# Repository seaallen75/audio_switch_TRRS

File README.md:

# audio_switch_TRRS
A 3.5mm TRRS audio switch, COM to A or B

I got tired of fumbling around under my desk to switch my audio connection between a headset and a speaker bar so I created a simple 3.5mm TRRS audio switch with KiCad and FreeCAD. 

The PCB was designed in KiCad. The gerbers can be found in gerbers/audio_switch_gerbers.zip and can be sent to any PCB fabricator. The PCB should be made 1.6mm thick to fit with the case. The [toggle switch](https://www.digikey.com/en/products/detail/e-switch/1003P1T1B1M2QEH/378894) and [3.5mm audio jacks](https://www.digikey.com/en/products/detail/tensility-international-corp/54-00174/12140150) are soldered to the PCB. 

The case was designed in FreeCAD. The .step models are available as well as a Bambu Studio file (.3mf) for printing on a Bambu 3D printer. M2.5x4x3.5 threaded heat-set inserts are pressed into the front piece of the case. A vertical heat-set insert press tool makes it much easier to install all of the threaded inserts straight up and down. The back piece of the case is secured with M2.5x10 screws. The case is designed to be mounted with Kreg pocket-hole screws.

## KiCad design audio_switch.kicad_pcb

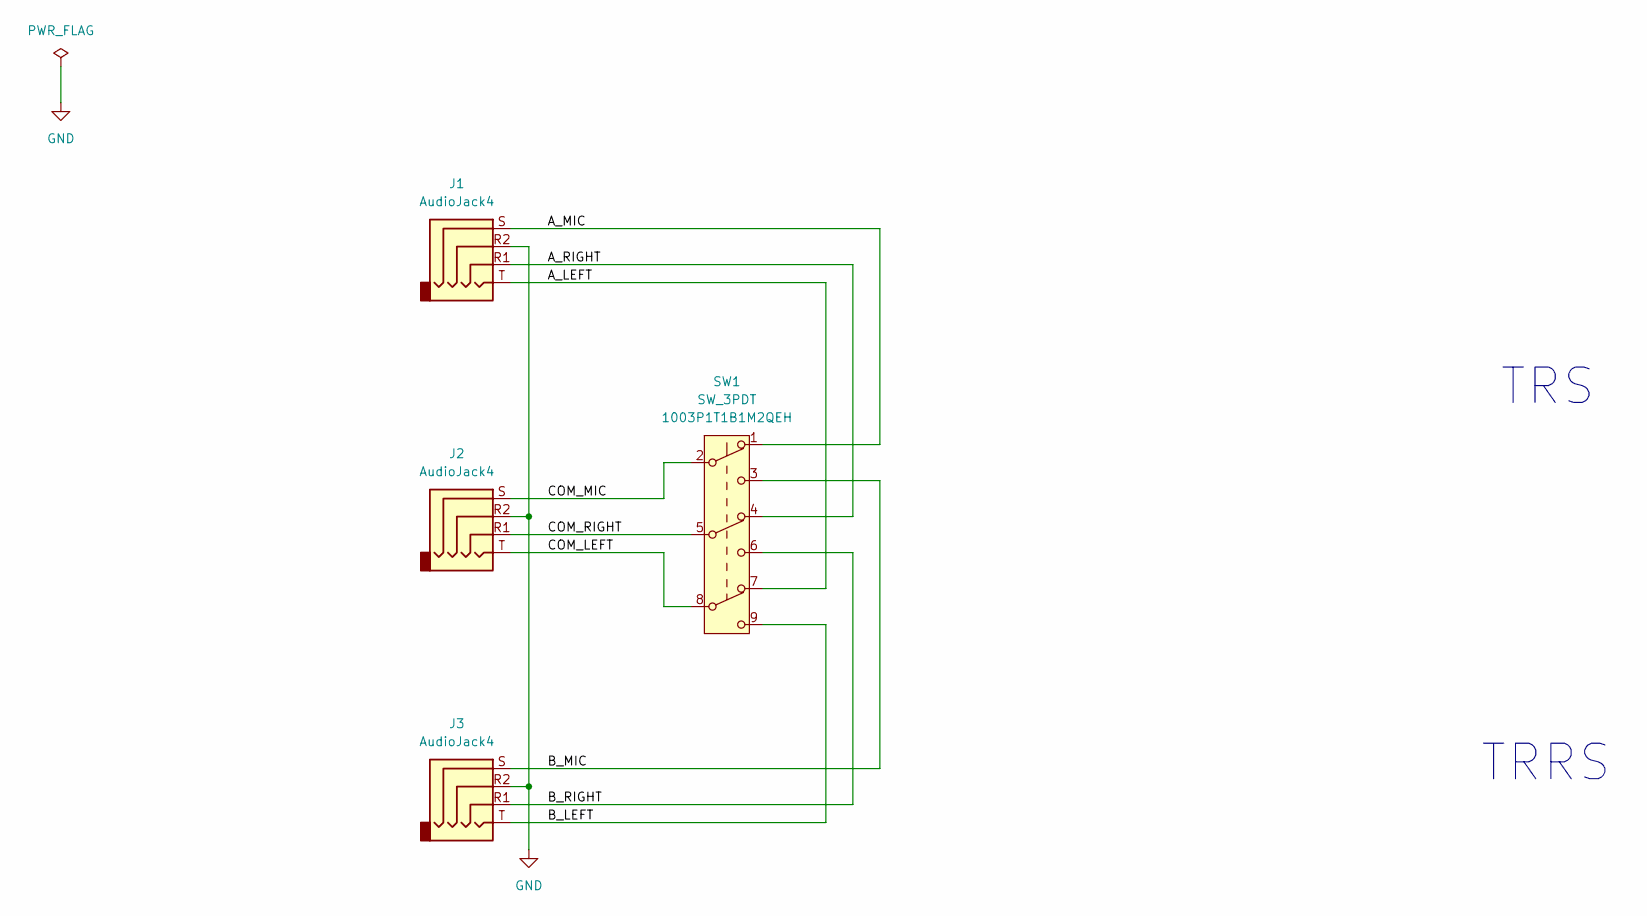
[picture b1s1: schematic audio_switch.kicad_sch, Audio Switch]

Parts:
J1, J2, J3: AudioJack4; 54-00174; MPN 54-00174
SW1: SW_3PDT; 1003P1T1B1M2QEH; MPN 1003P1T1B1M2QEH

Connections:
/A_LEFT: J1.T, SW1.7 (A)
/A_MIC: J1.S, SW1.1 (A)
/A_RIGHT: J1.R1, SW1.4 (A)
/B_LEFT: J3.T, SW1.9 (C)
/B_MIC: J3.S, SW1.3 (C)
/B_RIGHT: J3.R1, SW1.6 (C)
/COM_LEFT: J2.T, SW1.8 (B)
/COM_MIC: J2.S, SW1.2 (B)
/COM_RIGHT: J2.R1, SW1.5 (B)
GND: J1.R2, J2.R2, J3.R2

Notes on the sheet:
TRS
TRRS

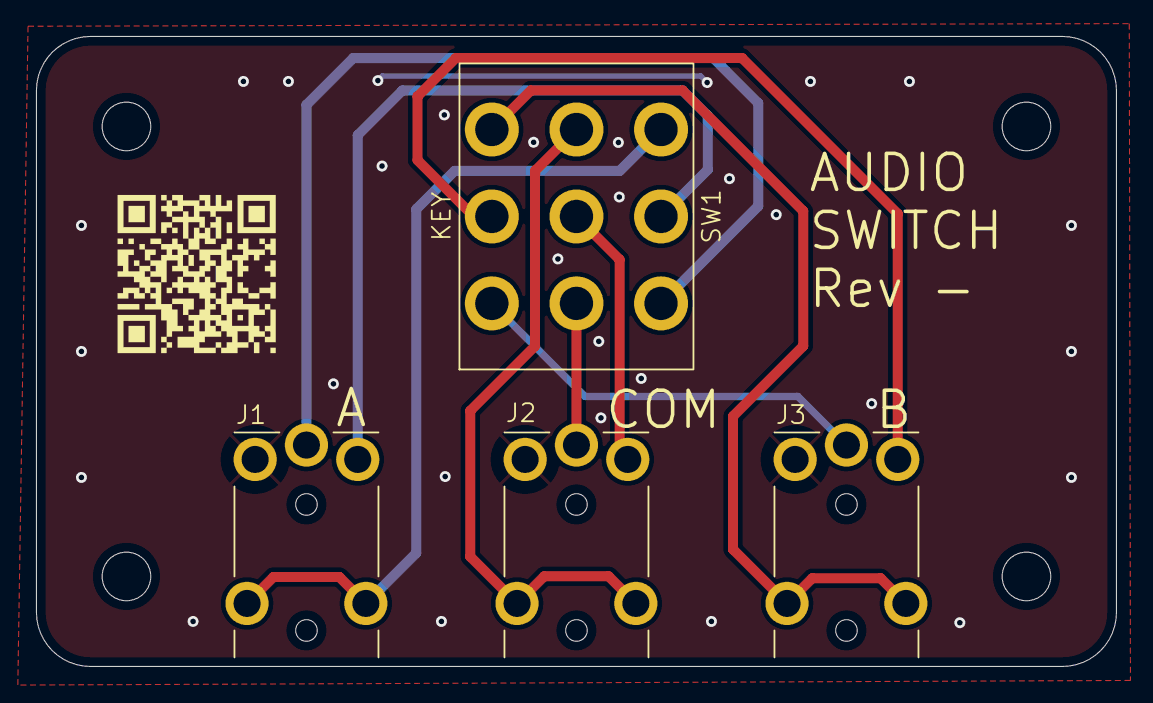
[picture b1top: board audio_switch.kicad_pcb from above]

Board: 2 copper layers, 60.0 x 35.0 mm, 4 parts (0 on the bottom side), 10 nets.

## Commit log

2025-11-14 Initial commit, added files via upload
